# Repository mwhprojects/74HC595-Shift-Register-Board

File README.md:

# 74HC595 Shift Register Board
Eagle board and schematic files for chain-able 74HC595 shift register boards.

Currently available on Tindie: https://www.tindie.com/products/mwhelectronics/chainable-16-channel-shift-register-board/

## License Information
<br />This work is licensed under a <a rel="license" href="http://creativecommons.org/licenses/by-sa/4.0/">Creative Commons Attribution-ShareAlike 4.0 International License</a>.

Distributed as-is; no warranty is given.

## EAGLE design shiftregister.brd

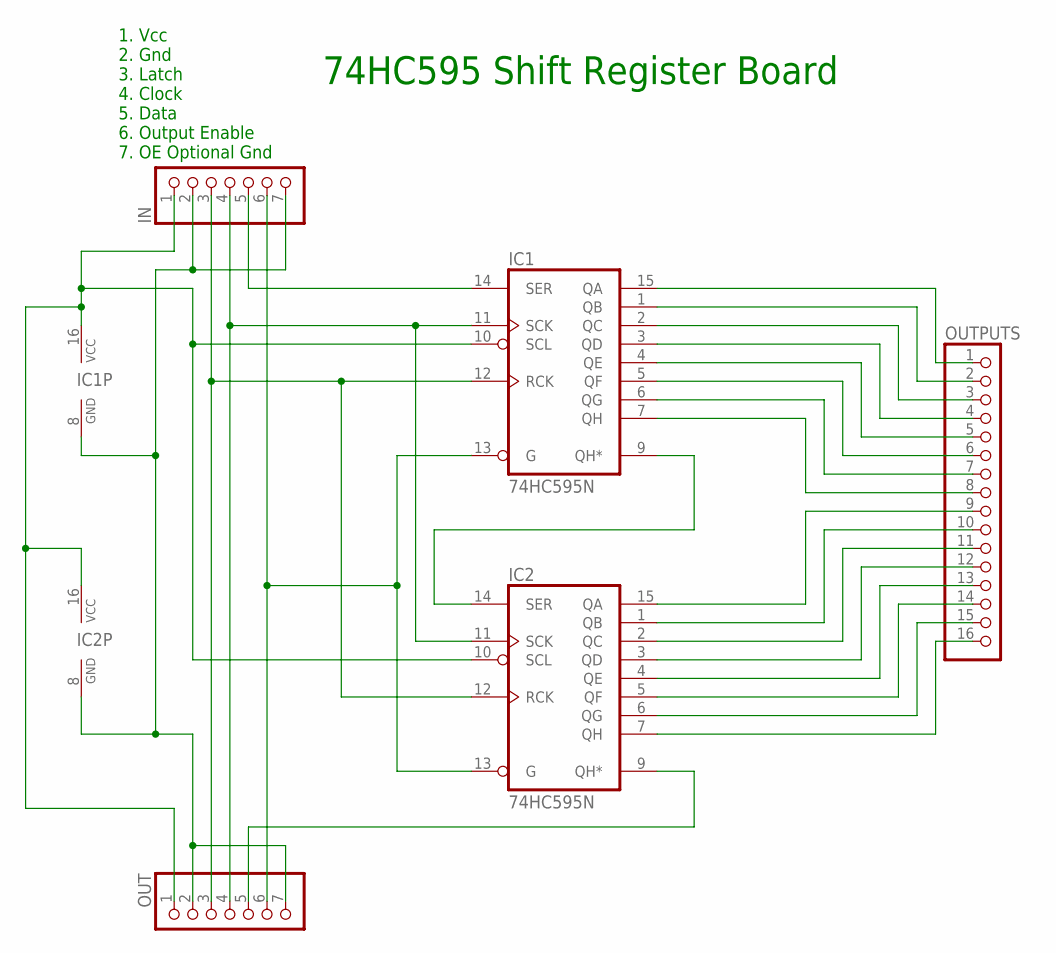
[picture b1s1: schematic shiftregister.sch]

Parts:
IC1, IC2: 74HC595N; DIL16
IN: PINHD-1X7; 1X07
OUT: PINHD-1X7; 1X07
OUTPUTS: PINHD-1X16; 1X16

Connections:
GND: IC1.8 (GND), IC2.8 (GND), IN.2, IN.7, OUT.2, OUT.7
unnamed: IC1.15 (QA), OUTPUTS.1
unnamed: IC1.1 (QB), OUTPUTS.2
unnamed: IC1.2 (QC), OUTPUTS.3
unnamed: IC1.3 (QD), OUTPUTS.4
unnamed: IC1.4 (QE), OUTPUTS.5
unnamed: IC1.5 (QF), OUTPUTS.6
unnamed: IC1.6 (QG), OUTPUTS.7
unnamed: IC1.7 (QH), OUTPUTS.8
unnamed: IC1.9 (QH*), IC2.14 (SER)
unnamed: IC1.14 (SER), IN.5
unnamed: IC2.9 (QH*), OUT.5
unnamed: IC1.13 (G), IC2.13 (G), IN.6, OUT.6
unnamed: IC1.12 (RCK), IC2.12 (RCK), IN.3, OUT.3
unnamed: IC1.11 (SCK), IC2.11 (SCK), IN.4, OUT.4
unnamed: IC2.15 (QA), OUTPUTS.9
unnamed: IC2.1 (QB), OUTPUTS.10
unnamed: IC2.2 (QC), OUTPUTS.11
unnamed: IC2.3 (QD), OUTPUTS.12
unnamed: IC2.4 (QE), OUTPUTS.13
unnamed: IC2.5 (QF), OUTPUTS.14
unnamed: IC2.6 (QG), OUTPUTS.15
unnamed: IC2.7 (QH), OUTPUTS.16
VCC: IC1.10 (SCL), IC1.16 (VCC), IC2.10 (SCL), IC2.16 (VCC), IN.1, OUT.1

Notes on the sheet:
1. Vcc 2. Gnd 3. Latch 4. Clock 5. Data 6. Output Enable 7. OE Optional Gnd
74HC595 Shift Register Board

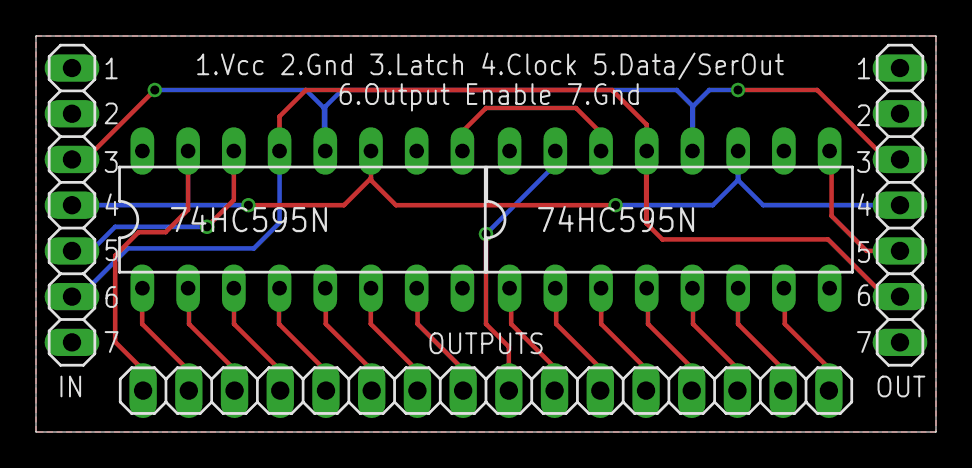
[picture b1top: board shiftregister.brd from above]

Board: 2 copper layers, 50.0 x 22.0 mm, 5 parts (0 on the bottom side), 24 nets.

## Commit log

2015-05-09 :lollipop: Added .gitattributes & .gitignore files
2015-05-09 Initial Release
    Have at it!
